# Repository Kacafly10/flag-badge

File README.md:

# flag-badge

A dynamic badge of flags.

## F

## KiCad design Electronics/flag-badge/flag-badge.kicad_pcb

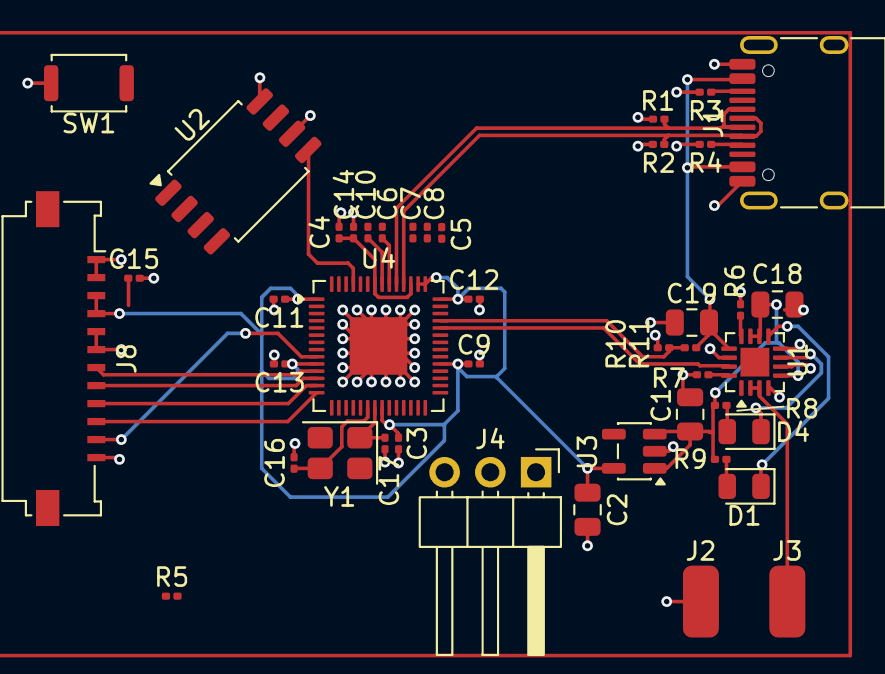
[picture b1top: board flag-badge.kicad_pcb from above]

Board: 2 copper layers, 43 parts (0 on the bottom side), 33 nets.

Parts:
C1, C2, C19: 1u; C_0805_2012Metric
C3, C4, C5, C9, C10, C11, C12, C13, C14, C15: 100n; C_0201_0603Metric
C6: 100nF; C_0201_0603Metric
C7, C8: 1u; C_0201_0603Metric
C16, C17: 27p; C_0201_0603Metric
C18: 4u7; C_0805_2012Metric
D1, D4: LED_Small; LED_0805_2012Metric
J1: USB_C_Receptacle_USB2.0_14P; USB_C_Receptacle_HRO_TYPE-C-31-M-12
J2, J3: Conn_01x01_Pin; SolderWirePad_1x01_SMD_2x4mm
J4: Conn_01x03_Pin; PinHeader_1x03_P2.54mm_Horizontal
J8: Conn_01x12_Pin; Molex_200528-0120_1x12-1MP_P1.00mm_Horizontal
R1, R2: 27; R_0201_0603Metric
R3, R4: 5.1k; R_0201_0603Metric
R5: 10k; R_0201_0603Metric
R6: 1k13; R_0201_0603Metric
R7: 1k18; R_0201_0603Metric
R8, R9, R11: 1k; R_0201_0603Metric
R10: 1k5; R_0201_0603Metric
SW1: SW_Push; SW_Push_SPST_NO_Alps_SKRK
U1: BQ24075RGT; VQFN-16-1EP_3x3mm_P0.5mm_EP1.6x1.6mm
U2: W25Q128JVS; SOIC-8_5.3x5.3mm_P1.27mm
U3: XC6220B331MR; SOT-23-5
U4: RP2040; QFN-56-1EP_7x7mm_P0.4mm_EP3.2x3.2mm
Y1: Crystal_GND24; Crystal_SMD_3225-4Pin_3.2x2.5mm

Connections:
/+3v3: C2.1, C3.1, C5.1, C6.1, C8.1, C9.1, C10.1, C11.1, C12.1, C13.1, C15.1, J8.3, J8.4, R5.1, U2.8 (VCC), U3.5 (VOUT), U4.1 (IOVDD), U4.10 (IOVDD), U4.22 (IOVDD), U4.33 (IOVDD), U4.42 (IOVDD), U4.43 (ADC_AVDD), U4.44 (VREG_VIN), U4.48 (USB_VDD), U4.49 (IOVDD)
/+5V: C1.1, C18.1, R8.2, R9.2, U1.5 (EN2), U1.10 (OUT), U1.11 (OUT), U3.1 (VIN), U3.3 (CE)
/BAT+: J3.1 (Pin_1_1), U1.2 (BAT), U1.3 (BAT)
/BOOTSEL: R5.2, SW1.1, U2.1 (~CS), U4.56 (~QSPI_SS)
/SWCLK: J4.1, U4.24 (SWCLK)
/SWDIO: J4.3, U4.25 (SWDIO)
/SYSOFF: U1.15 (SYSOFF), U4.38 (GPIO26/ADC0)
/TFT_CS: J8.8, U4.12 (GPIO9)
/TFT_D/C: J8.7, U4.11 (GPIO8)
/TFT_RESET: J8.11, U4.9 (GPIO7)
/TFT_SCL: J8.9, U4.13 (GPIO10)
/TFT_SDA: J8.10, U4.14 (GPIO11)
/USB_5V: C19.1, J1.A4 (VBUS), J1.A9 (VBUS), J1.B4 (VBUS), J1.B9 (VBUS), R11.2, U1.13 (IN)
/USB_D+: J1.A6 (D+), J1.B6 (D+), R1.1, U4.47 (USB_DP)
/USB_D-: J1.A7 (D-), J1.B7 (D-), R2.1, U4.46 (USB_DM)
GND: C1.2, C2.2, C3.2, C4.2, C5.2, C6.2, C7.2, C8.2, C9.2, C10.2, C11.2, C12.2, C13.2, C14.2, C15.2, C16.2, C17.2, C18.2, C19.2, J1.A1 (GND), J1.A12 (GND), J1.B1 (GND), J1.B12 (GND), J1.SH (SHIELD), J2.1 (Pin_1_1), J4.2, J8.1, J8.2, J8.5, J8.6, J8.12, R1.2, R2.2, R3.2, R4.2, R6.2, R7.2, R10.1, SW1.2, U1.4 (~CE), U1.6 (EN1), U1.8 (VSS), U1.14 (TMR), U1.17 (VSS), U2.4 (GND), U3.2 (GND), U4.57 (GND), Y1.2 (G), Y1.4 (G)
unnamed: D1.2 (A), R9.1
unnamed: D1.1 (K), U1.9 (~CHG)
unnamed: D4.2 (A), R8.1
unnamed: D4.1 (K), U1.7 (~PGOOD)
unnamed: J1.A5 (CC1), R4.1
unnamed: J1.B5 (CC2), R3.1
unnamed: R6.1, U1.12 (ILIM)
unnamed: R7.1, U1.16 (ISET)
unnamed: U2.6 (CLK), U4.52 (QSPI_SCLK)
unnamed: U2.5 (DI/IO_{0}), U4.53 (QSPI_SD0)
unnamed: U2.2 (DO/IO_{1}), U4.55 (QSPI_SD1)
unnamed: U2.7 (~HOLD/~RESET/IO_{3}), U4.51 (QSPI_SD3)
unnamed: U2.3 (~WP/IO_{2}), U4.54 (QSPI_SD2)
unnamed: R10.2, R11.1, U4.39 (GPIO27/ADC1)
unnamed: C4.1, C7.1, C14.1, U4.23 (DVDD), U4.45 (VREG_VOUT), U4.50 (DVDD)
unnamed: C16.1, U4.20 (XIN), Y1.3
unnamed: C17.1, U4.21 (XOUT), Y1.1
